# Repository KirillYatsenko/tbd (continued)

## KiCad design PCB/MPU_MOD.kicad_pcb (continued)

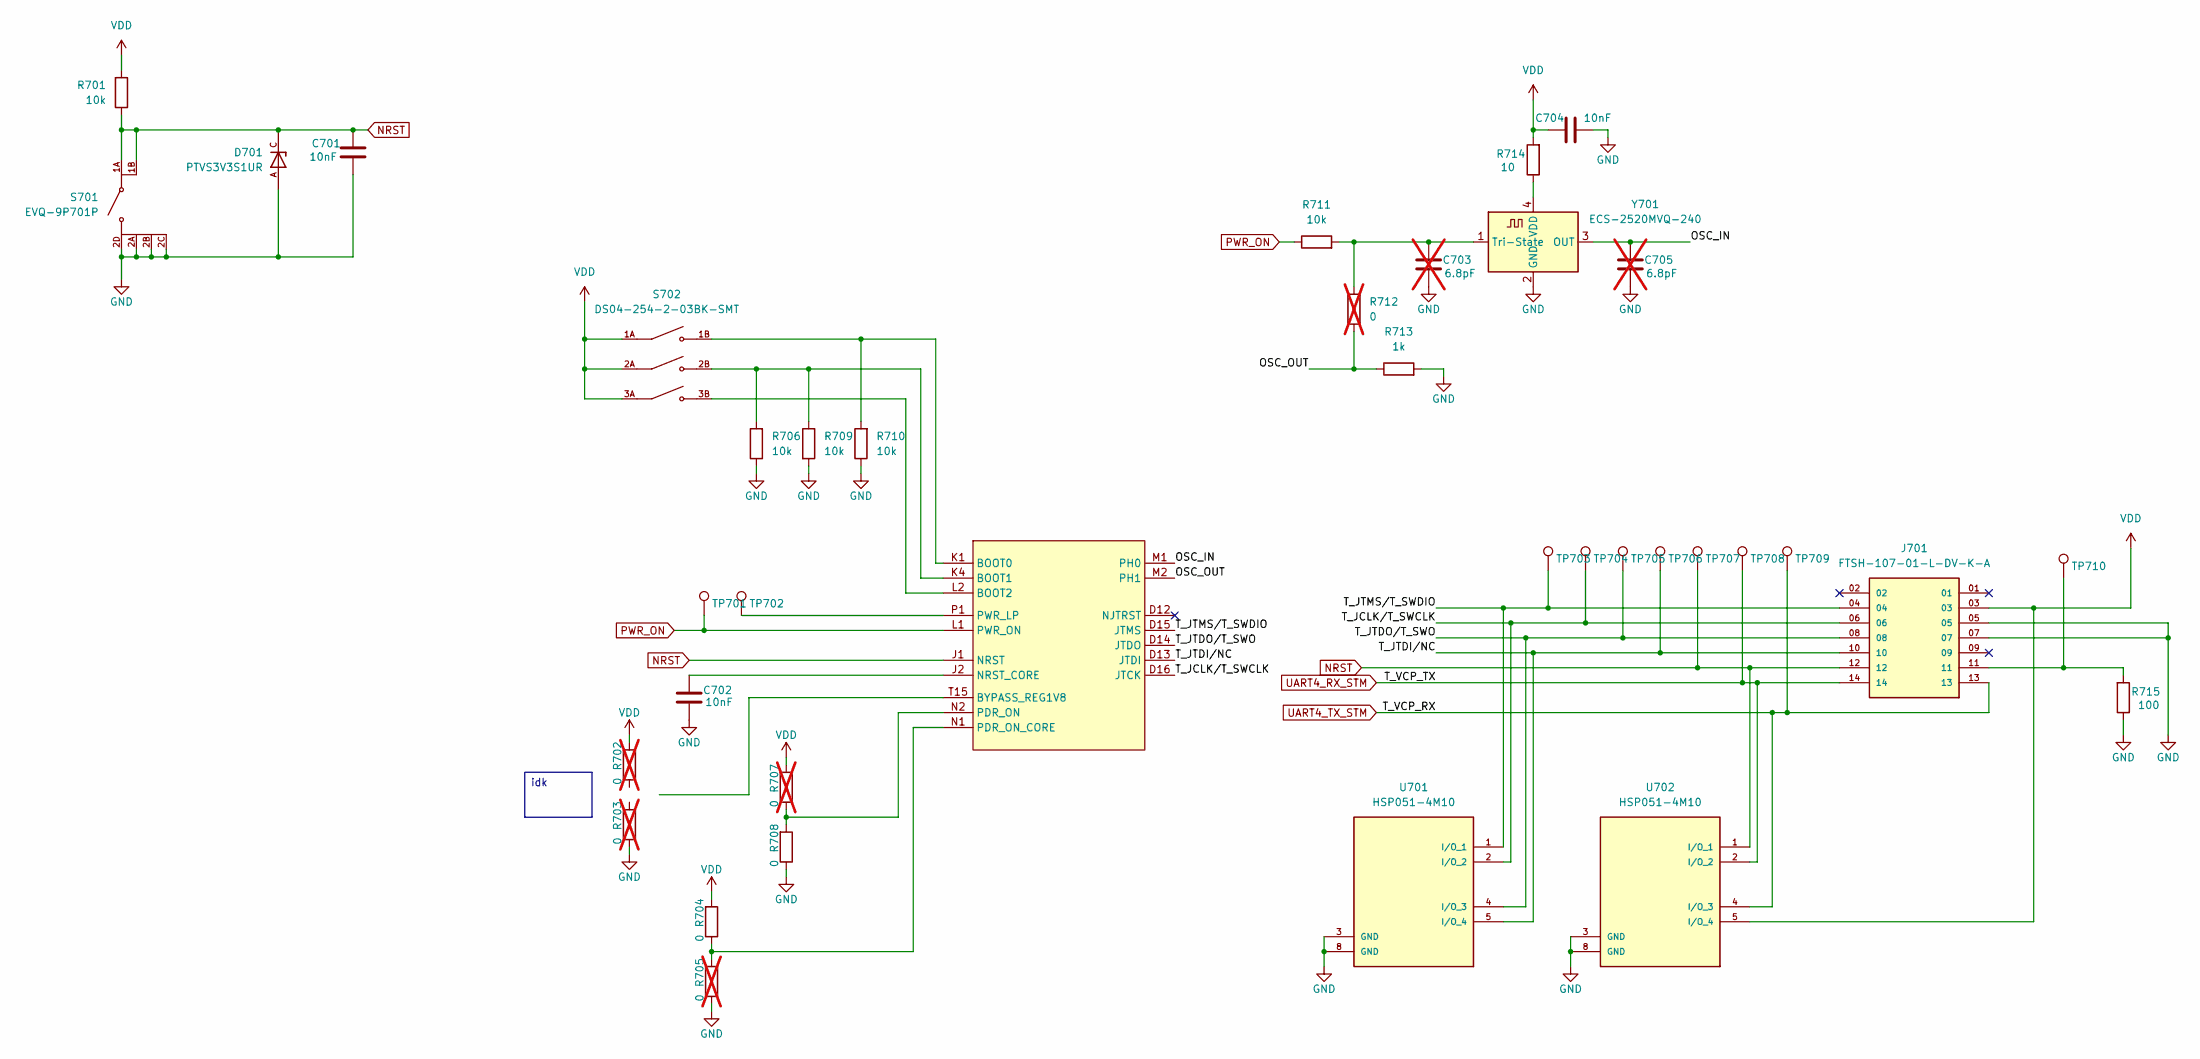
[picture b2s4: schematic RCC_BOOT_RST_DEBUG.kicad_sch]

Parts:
C701, C702, C704: 10nF; C_0402_1005Metric; Mouser P/N 81-GRM155R71C103KA1J
C703, C705: 6.8pF; C_0402_1005Metric; not fitted
D701: PTVS3V3S1UR; TVS_PTVS3V3S1UR; PARTREV Rev. 3
J701: FTSH-107-01-L-DV-K-A; SAMTEC_FTSH-107-01-L-DV-K-A; PARTREV H
R701, R706, R709, R710, R711: 10k; R_0402_1005Metric
R702, R703, R705, R707, R712: 0; R_0402_1005Metric; not fitted
R704, R708: 0; R_0402_1005Metric
R713: 1k; R_0402_1005Metric
R714: 10; R_0402_1005Metric
R715: 100; R_0402_1005Metric
S701: EVQ-9P701P; SW_EVQ-9P701P; PARTREV N/A
S702: DS04-254-2-03BK-SMT; SW_DS04-254-2-03BK-SMT; PARTREV V0.0
TP701, TP702, TP703, TP704, TP705, TP706, TP707, TP708, TP709, TP710: TestPoint; TP_0.5mm
U301: STM32MP157FABx; ST_LFBGA-354_16x16mm_Layout19x19_P0.8mm
U701, U702: HSP051-4M10; IC_HSP051-4M10; Mouser P/N 511-HSP051-4M10
Y701: ECS-2520MVQ-240; Oscillator_SMD_ECS_2520MV-xxx-xx-4Pin_2.5x2.0mm; Mouser P/N 520-E2520MVQ240BSTR

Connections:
/RCC_BOOT_RST_DEBUG/OSC_IN: C705.2, U301.M1 (PH0), Y701.3 (OUT)
/RCC_BOOT_RST_DEBUG/OSC_OUT: R712.1, R713.1, U301.M2 (PH1)
/RCC_BOOT_RST_DEBUG/T_JCLK/T_SWCLK: J701.06, TP704.1, U301.D16 (JTCK), U701.2 (I/O_2), U701.9 (NC)
/RCC_BOOT_RST_DEBUG/T_JTDI/NC: J701.10, TP706.1, U301.D13 (JTDI), U701.5 (I/O_4), U701.6 (NC)
/RCC_BOOT_RST_DEBUG/T_JTDO/T_SWO: J701.08, TP705.1, U301.D14 (JTDO), U701.4 (I/O_3), U701.7 (NC)
/RCC_BOOT_RST_DEBUG/T_JTMS/T_SWDIO: J701.04, TP703.1, U301.D15 (JTMS), U701.1 (I/O_1), U701.10 (NC)
GND: C701.1, C702.1, C703.1, C704.2, C705.1, D701.A, J701.05, J701.07, R703.1, R705.1, R706.1, R708.1, R709.2, R710.1, R713.2, R715.1, S701.2A, S701.2B, S701.2C, S701.2D, U701.3 (GND), U701.8 (GND), U702.3 (GND), U702.8 (GND), Y701.2 (GND); also elsewhere on the board
NRST: C701.2, D701.C, J701.12, R701.1, S701.1A, S701.1B, TP707.1, U301.J1 (NRST), U702.1 (I/O_1), U702.10 (NC); also elsewhere on the board
unnamed: J701.11, R715.2, TP710.1
unnamed: R710.2, S702.1B, U301.K1 (BOOT0)
unnamed: R706.2, R709.1, S702.2B, U301.K4 (BOOT1)
unnamed: S702.3B, U301.L2 (BOOT2)
unnamed: C702.2, U301.J2 (NRST_CORE)
unnamed: R707.1, R708.2, U301.N2 (PDR_ON)
unnamed: R704.1, R705.2, U301.N1 (PDR_ON_CORE)
unnamed: TP702.1, U301.P1 (PWR_LP)
unnamed: C703.2, R711.2, R712.2, Y701.1 (Tri-State)
unnamed: R714.1, Y701.4 (VDD)
PWR_ON: R711.1, TP701.1, U301.L1 (PWR_ON); also elsewhere on the board
UART4_RX_STM: J701.14, TP708.1, U702.2 (I/O_2), U702.9 (NC); also elsewhere on the board
UART4_TX_STM: J701.13, TP709.1, U702.4 (I/O_3), U702.7 (NC); also elsewhere on the board
VDD: C704.1, J701.03, R701.2, R702.2, R704.2, R707.2, R714.2, S702.1A, S702.2A, S702.3A, U702.5 (I/O_4), U702.6 (NC); also elsewhere on the board

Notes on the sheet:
idk

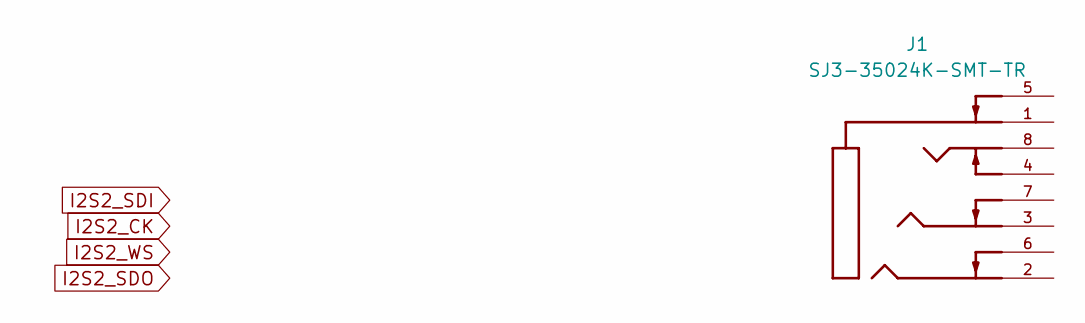
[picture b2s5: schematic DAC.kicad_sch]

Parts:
J1: SJ3-35024K-SMT-TR; SAMESKY_SJ3-35024K-SMT-TR; PARTREV 1.0

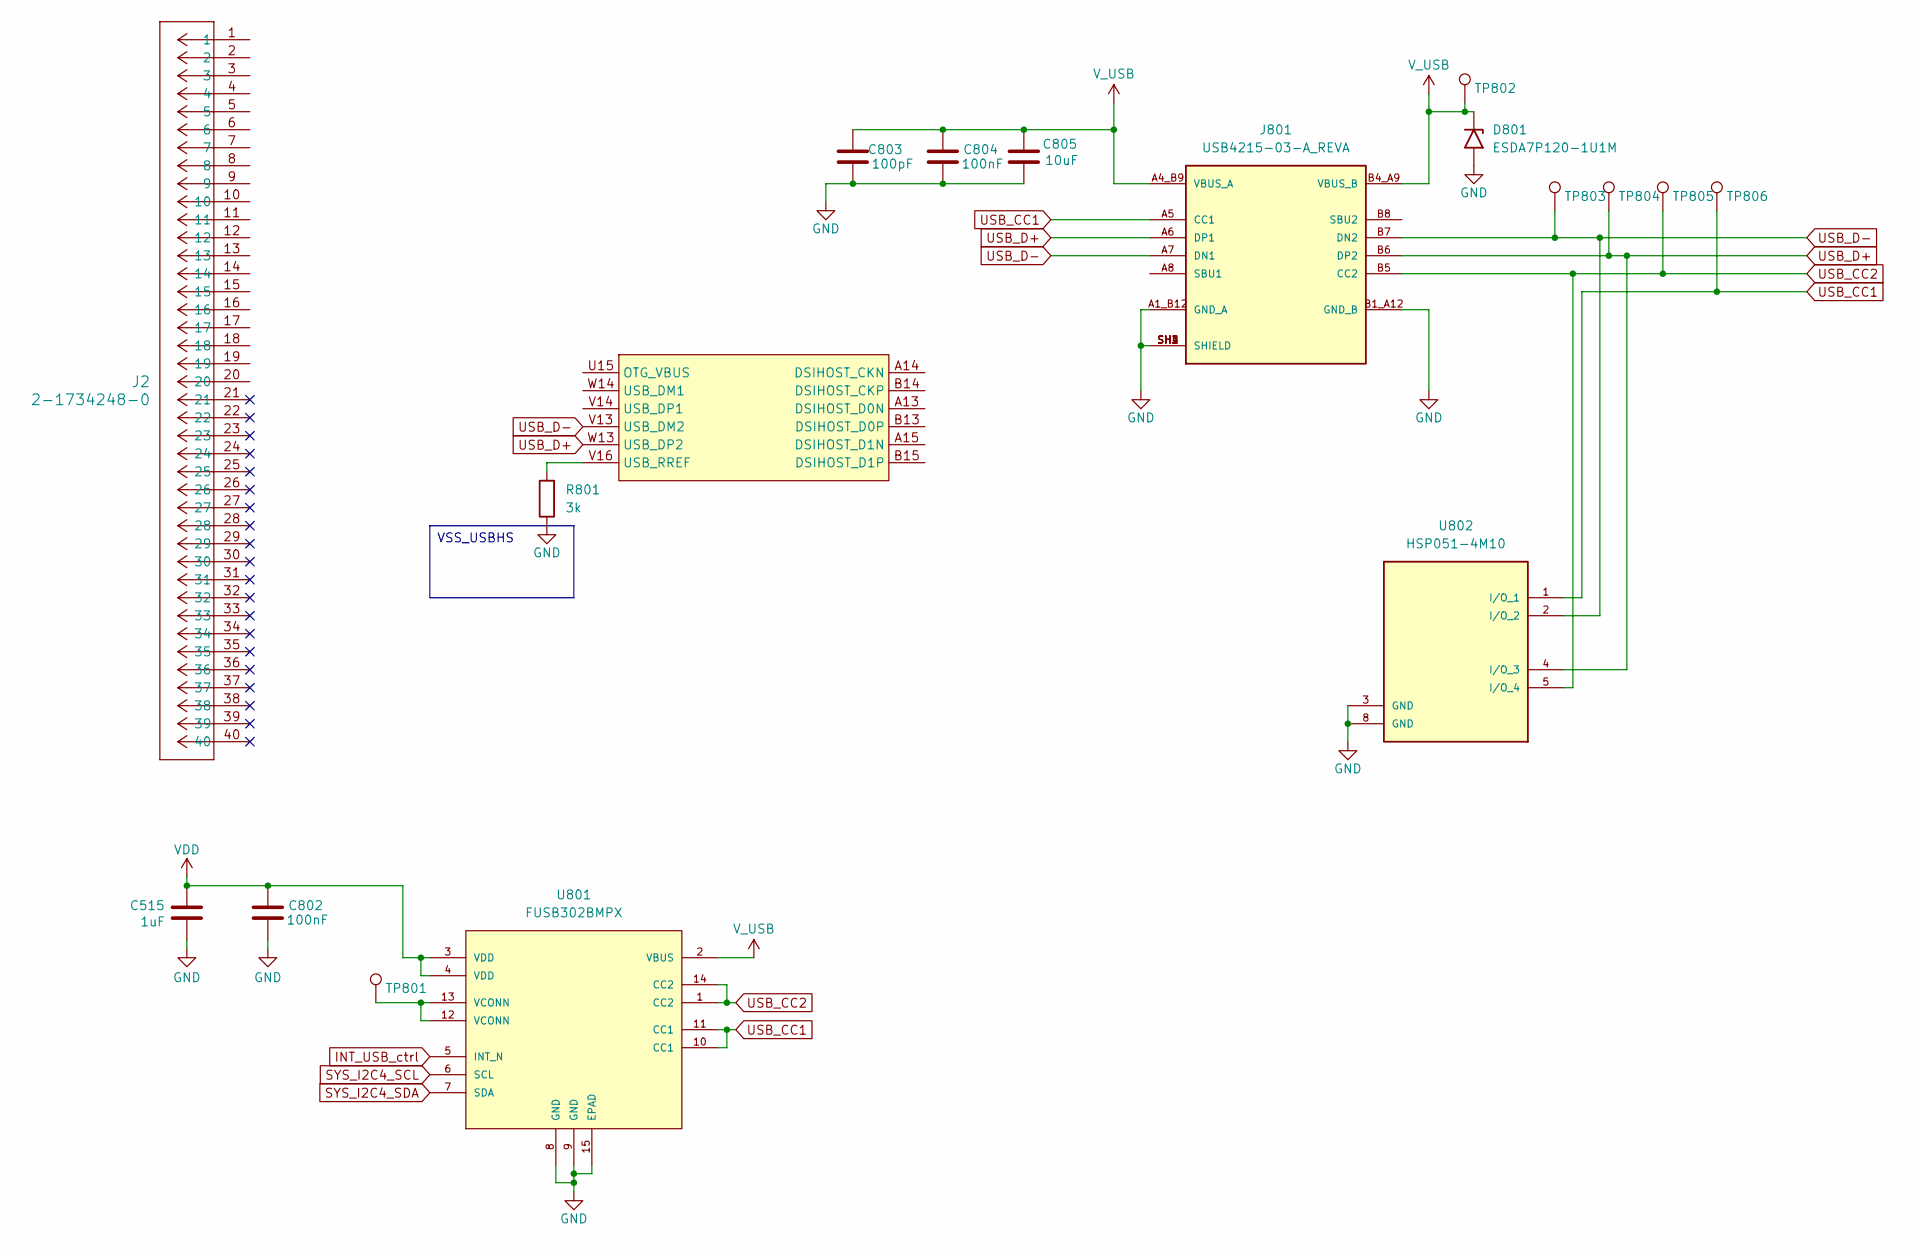
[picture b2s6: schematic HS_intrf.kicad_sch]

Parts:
C515: 1uF; C_0402_1005Metric; Mouser P/N 81-GRM155R61E105KA2D
C802, C804: 100nF; C_0402_1005Metric; Mouser P/N 81-GRM155R61E104KA7J
C803: 100pF; C_0402_1005Metric
C805: 10uF; C_0603_1608Metric; Mouser P/N 81-GRT188R61A106KE3D
D801: ESDA7P120-1U1M; DIODE_ESDA7P120-1U1M_STM
J2: 2-1734248-0; CONN_2-1734248-0_TYCO
J801: USB4215-03-A_REVA; GCT_USB4215-03-A_REVA; PARTREV A
R801: 3k; R_0402_1005Metric
TP801, TP802, TP803, TP804, TP805, TP806: TestPoint; TP_0.5mm
U301: STM32MP157FABx; ST_LFBGA-354_16x16mm_Layout19x19_P0.8mm
U801: FUSB302BMPX; MLP14_2P5X2P5_ONS; MANUFACTURER_PART_NUMBER FUSB302BMPX
U802: HSP051-4M10; IC_HSP051-4M10; Mouser P/N 511-HSP051-4M10

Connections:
GND: C515.2, C802.1, C803.2, C804.1, C805.1, D801.2 (A2), J801.A1_B12 (GND_A), J801.B1_A12 (GND_B), J801.SH1 (SHIELD), J801.SH2 (SHIELD), J801.SH3 (SHIELD), J801.SH4 (SHIELD), R801.1, U801.8 (GND), U801.9 (GND), U801.15 (EPAD), U802.3 (GND), U802.8 (GND); also elsewhere on the board
INT_USB_ctrl: U801.5 (INT_N)
unnamed: TP801.1, U801.12 (VCONN), U801.13 (VCONN)
unnamed: R801.2, U301.V16 (USB_RREF)
SYS_I2C4_SCL: U801.6 (SCL); also elsewhere on the board
SYS_I2C4_SDA: U801.7 (SDA); also elsewhere on the board
USB_CC1: J801.A5 (CC1), TP806.1, U801.10 (CC1), U801.11 (CC1), U802.1 (I/O_1), U802.10 (NC)
USB_CC2: J801.B5 (CC2), TP805.1, U801.1 (CC2), U801.14 (CC2), U802.5 (I/O_4), U802.6 (NC)
USB_D+: J801.A6 (DP1), J801.B6 (DP2), TP804.1, U301.W13 (USB_DP2), U802.4 (I/O_3), U802.7 (NC)
USB_D-: J801.A7 (DN1), J801.B7 (DN2), TP803.1, U301.V13 (USB_DM2), U802.2 (I/O_2), U802.9 (NC)
VDD: C515.1, C802.2, U801.3 (VDD), U801.4 (VDD); also elsewhere on the board
V_USB: C803.1, C804.2, C805.2, D801.1 (A1), J801.A4_B9 (VBUS_A), J801.B4_A9 (VBUS_B), TP802.1, U801.2 (VBUS); also elsewhere on the board

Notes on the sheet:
VSS_USBHS

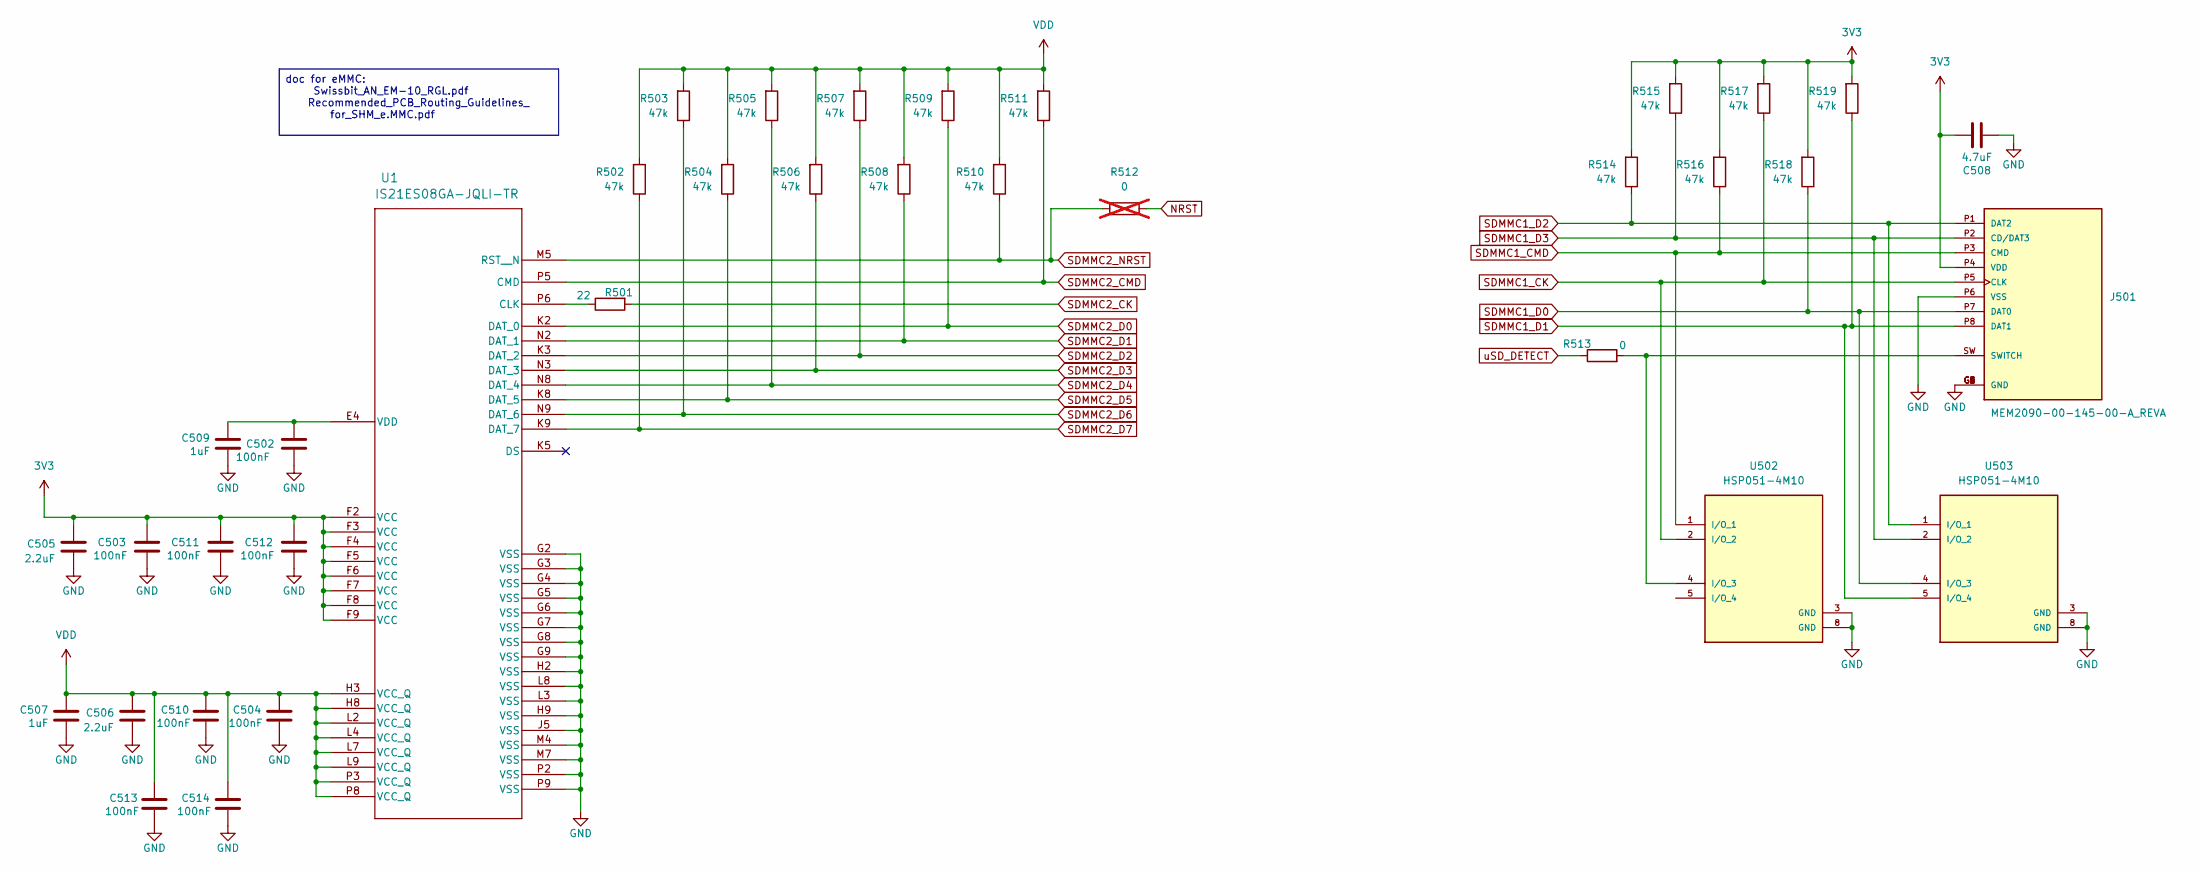
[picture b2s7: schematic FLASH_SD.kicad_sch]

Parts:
C502, C503, C504, C510, C511, C512, C513, C514: 100nF; C_0402_1005Metric; Mouser P/N 81-GRM155R61E104KA7J
C505, C506: 2.2uF; C_0402_1005Metric; Mouser P/N 81-GRT153R60J225ME3D
C507, C509: 1uF; C_0402_1005Metric; Mouser P/N 81-GRM155R61E105KA2D
C508: 4.7uF; C_0402_1005Metric; Mouser P/N 81-GRM155R60J475ME7J
J501: MEM2090-00-145-00-A_REVA; GCT_MEM2090-00-145-00-A_REVA; Mouser P/N 640-MEM20900014500A
R501: 22; R_0402_1005Metric
R502, R503, R504, R505, R506, R507, R508, R509, R510, R511, R514, R515, R516, R517, R518, R519: 47k; R_0402_1005Metric
R512: 0; R_0402_1005Metric; not fitted
R513: 0; R_0402_1005Metric
U1: IS21ES08GA-JQLI-TR; FBGA100_ISI
U502, U503: HSP051-4M10; IC_HSP051-4M10; Mouser P/N 511-HSP051-4M10

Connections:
3V3: C503.2, C505.1, C508.2, C511.2, C512.2, J501.P4 (VDD), R514.2, R515.2, R516.2, R517.2, R518.2, R519.2, U1.F2 (VCC), U1.F3 (VCC), U1.F4 (VCC), U1.F5 (VCC), U1.F6 (VCC), U1.F7 (VCC), U1.F8 (VCC), U1.F9 (VCC); also elsewhere on the board
GND: C502.1, C503.1, C504.1, C505.2, C506.2, C507.2, C508.1, C509.2, C510.1, C511.1, C512.1, C513.1, C514.1, J501.G1 (GND), J501.G2 (GND), J501.G3 (GND), J501.G4 (GND), J501.G5 (GND), J501.G6 (GND), J501.P6 (VSS), U1.G2 (VSS), U1.G3 (VSS), U1.G4 (VSS), U1.G5 (VSS), U1.G6 (VSS), U1.G7 (VSS), U1.G8 (VSS), U1.G9 (VSS), U1.H2 (VSS), U1.H9 (VSS), U1.J5 (VSS), U1.L3 (VSS), U1.L8 (VSS), U1.M4 (VSS), U1.M7 (VSS), U1.P2 (VSS), U1.P9 (VSS), U502.3 (GND), U502.8 (GND), U503.3 (GND), U503.8 (GND); also elsewhere on the board
NRST: R512.1; also elsewhere on the board
unnamed: J501.SW (SWITCH), R513.2, U502.4 (I/O_3), U502.7 (NC)
unnamed: R501.1, U1.P6 (CLK)
unnamed: C502.2, C509.1, U1.E4 (VDD)
unnamed: U502.5 (I/O_4), U502.6 (NC)
SDMMC1_CK: J501.P5 (CLK), R517.1, U502.2 (I/O_2), U502.9 (NC); also elsewhere on the board
SDMMC1_CMD: J501.P3 (CMD), R516.1, U502.1 (I/O_1), U502.10 (NC); also elsewhere on the board
SDMMC1_D0: J501.P7 (DAT0), R518.1, U503.4 (I/O_3), U503.7 (NC); also elsewhere on the board
SDMMC1_D1: J501.P8 (DAT1), R519.1, U503.5 (I/O_4), U503.6 (NC); also elsewhere on the board
SDMMC1_D2: J501.P1 (DAT2), R514.1, U503.1 (I/O_1), U503.10 (NC); also elsewhere on the board
SDMMC1_D3: J501.P2 (CD/DAT3), R515.1, U503.2 (I/O_2), U503.9 (NC); also elsewhere on the board
SDMMC2_CK: R501.2; also elsewhere on the board
SDMMC2_CMD: R511.1, U1.P5 (CMD); also elsewhere on the board
SDMMC2_D0: R509.1, U1.K2 (DAT_0); also elsewhere on the board
SDMMC2_D1: R508.1, U1.N2 (DAT_1); also elsewhere on the board
SDMMC2_D2: R507.1, U1.K3 (DAT_2); also elsewhere on the board
SDMMC2_D3: R506.1, U1.N3 (DAT_3); also elsewhere on the board
SDMMC2_D4: R505.1, U1.N8 (DAT_4); also elsewhere on the board
SDMMC2_D5: R504.1, U1.K8 (DAT_5); also elsewhere on the board
SDMMC2_D6: R503.1, U1.N9 (DAT_6); also elsewhere on the board
SDMMC2_D7: R502.1, U1.K9 (DAT_7); also elsewhere on the board
SDMMC2_NRST: R510.1, R512.2, U1.M5 (RST__N)
VDD: C504.2, C506.1, C507.1, C510.2, C513.2, C514.2, R502.2, R503.2, R504.2, R505.2, R506.2, R507.2, R508.2, R509.2, R510.2, R511.2, U1.H3 (VCC_Q), U1.H8 (VCC_Q), U1.L2 (VCC_Q), U1.L4 (VCC_Q), U1.L7 (VCC_Q), U1.L9 (VCC_Q), U1.P3 (VCC_Q), U1.P8 (VCC_Q); also elsewhere on the board
uSD_DETECT: R513.1; also elsewhere on the board

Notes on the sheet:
doc for eMMC: Swissbit_AN_EM-10_RGL.pdf Recommended_PCB_Routing_Guidelines_ for_SHM_e.MMC.pdf

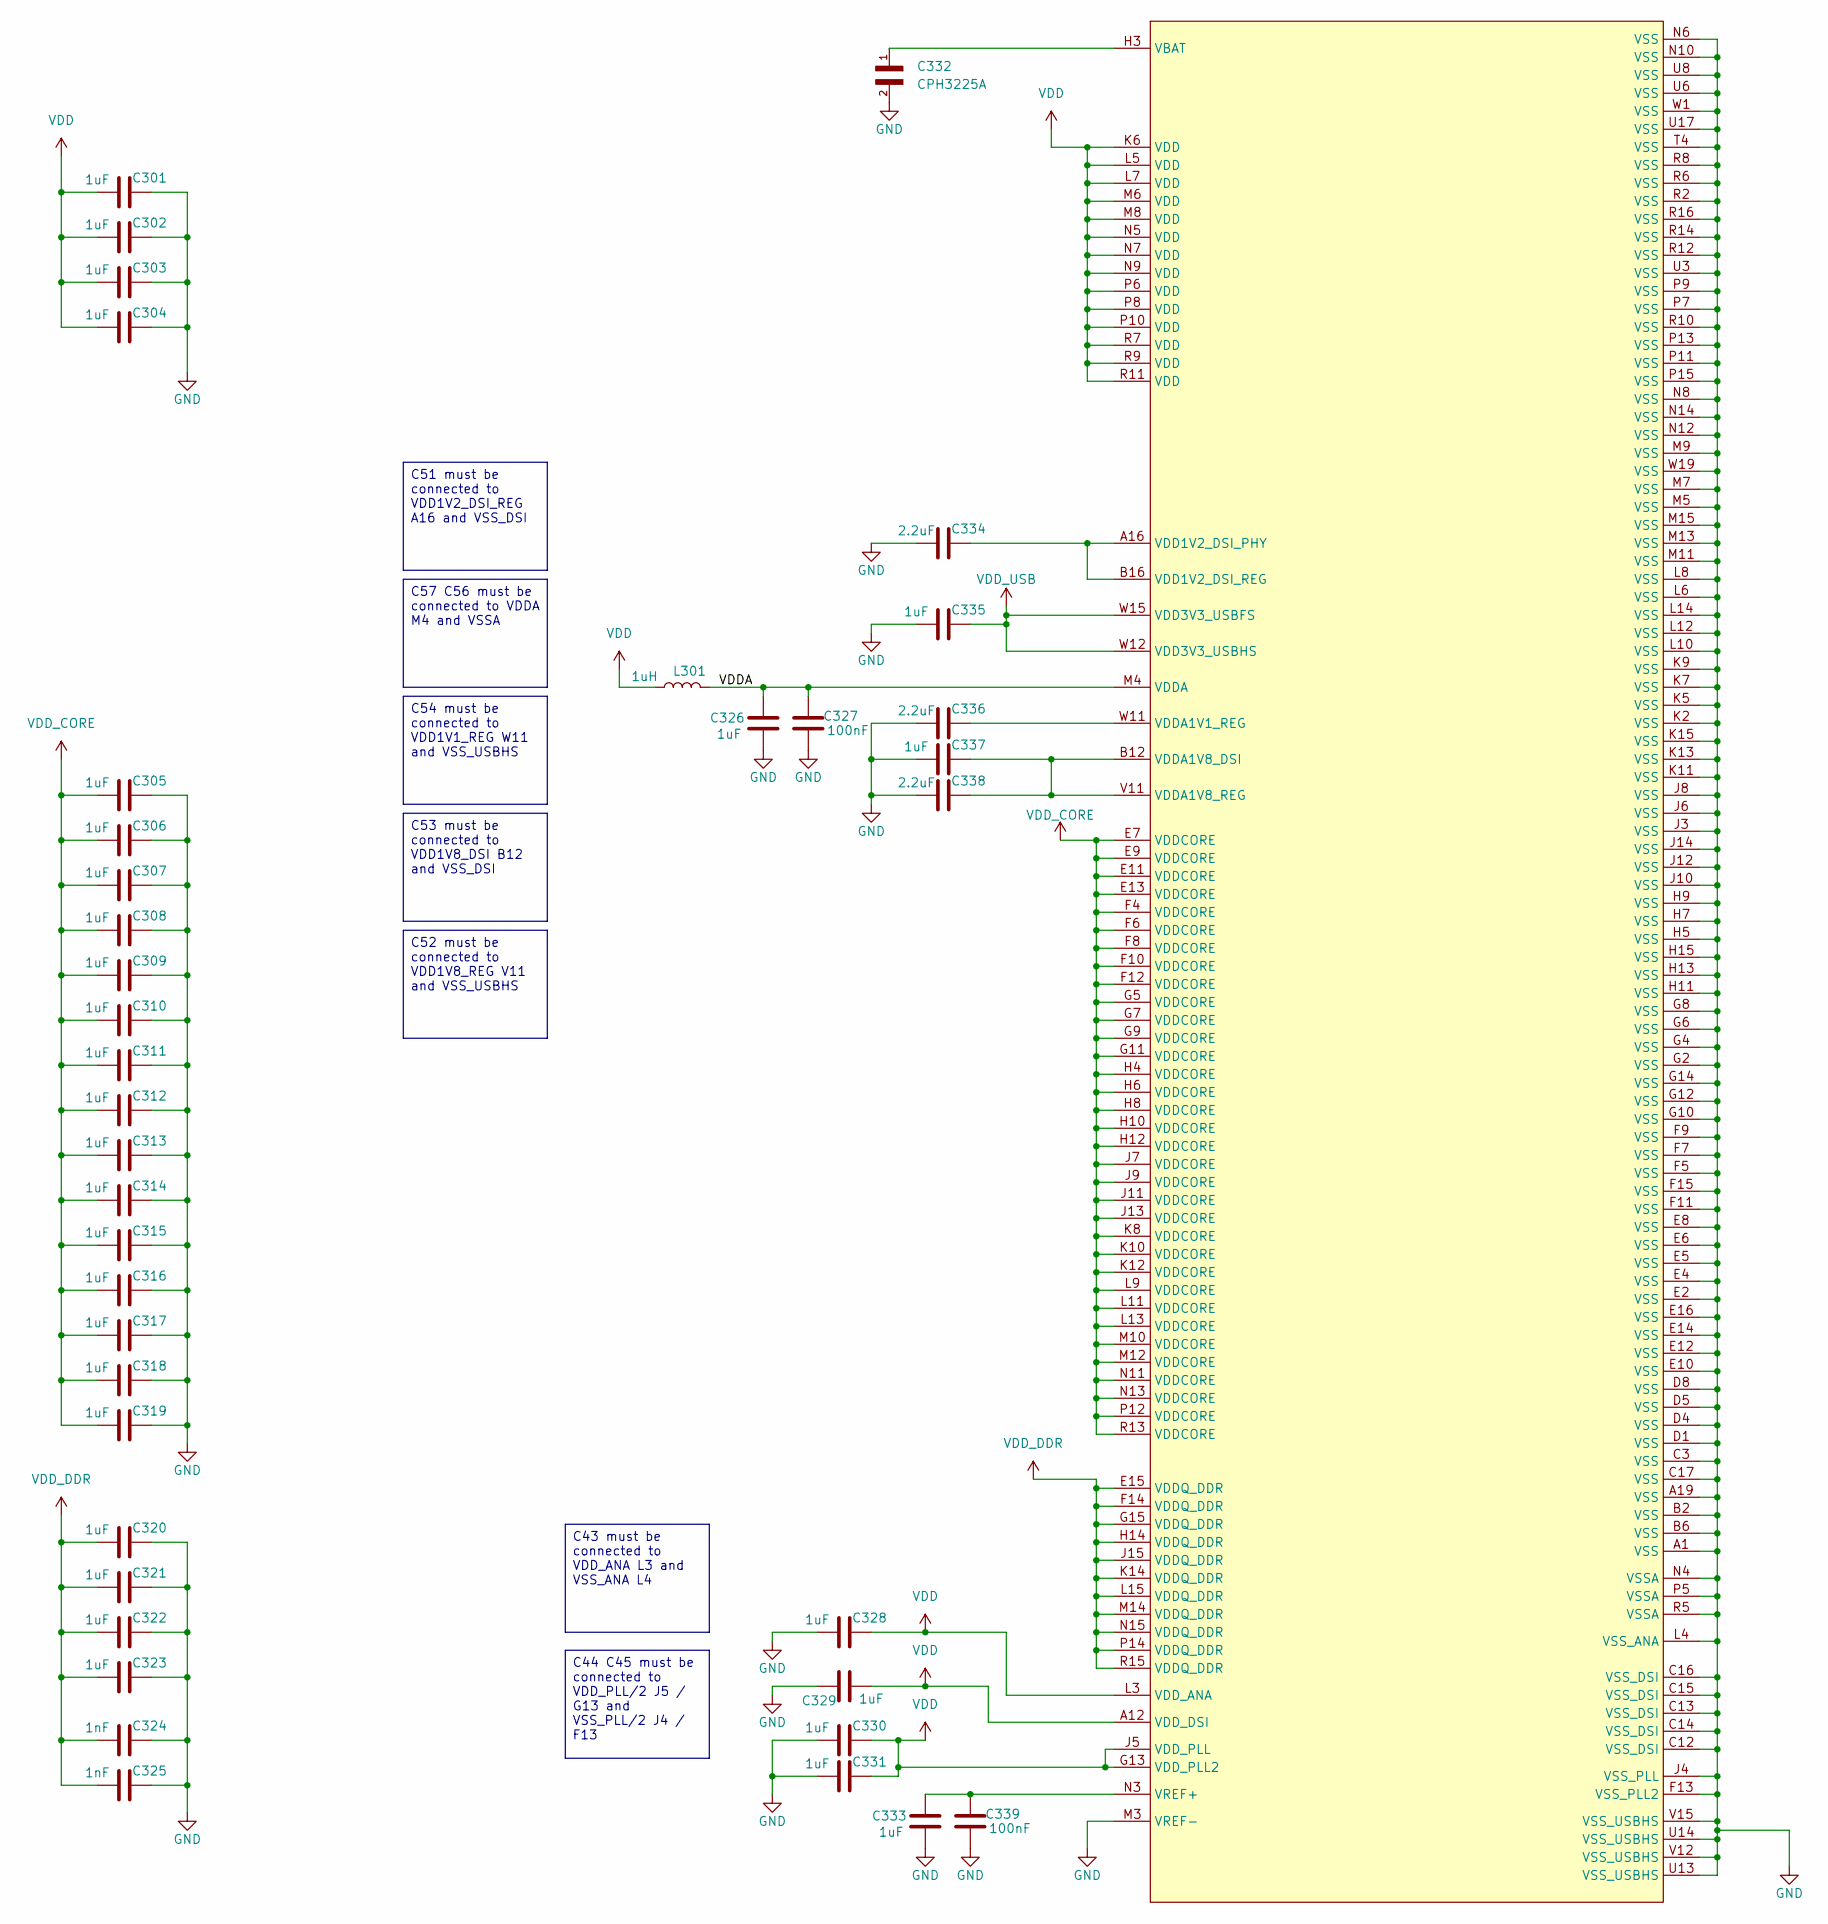
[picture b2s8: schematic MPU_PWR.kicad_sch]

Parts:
C301, C302, C303, C304, C305, C306, C307, C308, C309, C310, C311, C312, C313, C314, C315, C316, C317, C318, C319, C320, C321, C322, C323, C326, C328, C329, C330, C331, C333, C335, C337: 1uF; C_0402_1005Metric; Mouser P/N 81-GRM155R61E105KA2D
C324, C325: 1nF; C_0402_1005Metric; Mouser P/N 81-GRM155R70J102KA1D
C327, C339: 100nF; C_0402_1005Metric; Mouser P/N 81-GRM155R61E104KA7J
C332: CPH3225A; CAPCP3225X100N
C334, C336, C338: 2.2uF; C_0402_1005Metric; Mouser P/N 81-GRT153R60J225ME3D
L301: 1uH; L_0603_1608Metric; Mouser P/N 810-MLZ1608M4R7WT000
U301: STM32MP157FABx; ST_LFBGA-354_16x16mm_Layout19x19_P0.8mm

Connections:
GND: C301.1, C302.1, C303.1, C304.1, C305.1, C306.1, C307.1, C308.1, C309.1, C310.1, C311.1, C312.1, C313.1, C314.1, C315.1, C316.1, C317.1, C318.1, C319.1, C320.1, C321.1, C322.1, C323.1, C324.1, C325.1, C326.2, C327.2, C328.2, C329.1, C330.2, C331.2, C332.2, C333.2, C334.2, C335.2, C336.2, C337.2, C338.2, C339.2, U301.A1 (VSS), U301.A19 (VSS), U301.B2 (VSS), U301.B6 (VSS), U301.C3 (VSS), U301.C12 (VSS_DSI), U301.C13 (VSS_DSI), U301.C14 (VSS_DSI), U301.C15 (VSS_DSI), U301.C16 (VSS_DSI), U301.C17 (VSS), U301.D1 (VSS), U301.D4 (VSS), U301.D5 (VSS), U301.D8 (VSS), U301.E2 (VSS), U301.E4 (VSS), U301.E5 (VSS), U301.E6 (VSS), U301.E8 (VSS), U301.E10 (VSS), U301.E12 (VSS), U301.E14 (VSS), U301.E16 (VSS), U301.F5 (VSS), U301.F7 (VSS), U301.F9 (VSS), U301.F11 (VSS), U301.F13 (VSS_PLL2), U301.F15 (VSS), U301.G2 (VSS), U301.G4 (VSS), U301.G6 (VSS), U301.G8 (VSS), U301.G10 (VSS), U301.G12 (VSS), U301.G14 (VSS), U301.H5 (VSS), U301.H7 (VSS), U301.H9 (VSS), U301.H11 (VSS), U301.H13 (VSS), U301.H15 (VSS), U301.J3 (VSS), U301.J4 (VSS_PLL), U301.J6 (VSS), U301.J8 (VSS), U301.J10 (VSS), U301.J12 (VSS), U301.J14 (VSS), U301.K2 (VSS), U301.K5 (VSS), U301.K7 (VSS), U301.K9 (VSS), U301.K11 (VSS), U301.K13 (VSS), U301.K15 (VSS), U301.L4 (VSS_ANA), U301.L6 (VSS), U301.L8 (VSS), U301.L10 (VSS), U301.L12 (VSS), U301.L14 (VSS), U301.M3 (VREF-), U301.M5 (VSS), U301.M7 (VSS), U301.M9 (VSS), U301.M11 (VSS), U301.M13 (VSS), U301.M15 (VSS), U301.N4 (VSSA), U301.N6 (VSS), U301.N8 (VSS), U301.N10 (VSS), U301.N12 (VSS), U301.N14 (VSS), U301.P5 (VSSA), U301.P7 (VSS), U301.P9 (VSS), U301.P11 (VSS), U301.P13 (VSS), U301.P15 (VSS), U301.R2 (VSS), U301.R5 (VSSA), U301.R6 (VSS), U301.R8 (VSS), U301.R10 (VSS), U301.R12 (VSS), U301.R14 (VSS), U301.R16 (VSS), U301.T4 (VSS), U301.U3 (VSS), U301.U6 (VSS), U301.U8 (VSS), U301.U13 (VSS_USBHS), U301.U14 (VSS_USBHS), U301.U17 (VSS), U301.V12 (VSS_USBHS), U301.V15 (VSS_USBHS), U301.W1 (VSS), U301.W19 (VSS); also elsewhere on the board
unnamed: C332.1, U301.H3 (VBAT)
unnamed: C334.1, U301.A16 (VDD1V2_DSI_PHY), U301.B16 (VDD1V2_DSI_REG)
unnamed: C336.1, U301.W11 (VDDA1V1_REG)
unnamed: C337.1, C338.1, U301.B12 (VDDA1V8_DSI), U301.V11 (VDDA1V8_REG)
unnamed: C326.1, C327.1, L301.2, U301.M4 (VDDA)
unnamed: C333.1, C339.1, U301.N3 (VREF+)
VDD: C301.2, C302.2, C303.2, C304.2, C328.1, C329.2, C330.1, C331.1, L301.1, U301.A12 (VDD_DSI), U301.G13 (VDD_PLL2), U301.J5 (VDD_PLL), U301.K6 (VDD), U301.L3 (VDD_ANA), U301.L5 (VDD), U301.L7 (VDD), U301.M6 (VDD), U301.M8 (VDD), U301.N5 (VDD), U301.N7 (VDD), U301.N9 (VDD), U301.P6 (VDD), U301.P8 (VDD), U301.P10 (VDD), U301.R7 (VDD), U301.R9 (VDD), U301.R11 (VDD); also elsewhere on the board
VDD_CORE: C305.2, C306.2, C307.2, C308.2, C309.2, C310.2, C311.2, C312.2, C313.2, C314.2, C315.2, C316.2, C317.2, C318.2, C319.2, U301.E7 (VDDCORE), U301.E9 (VDDCORE), U301.E11 (VDDCORE), U301.E13 (VDDCORE), U301.F4 (VDDCORE), U301.F6 (VDDCORE), U301.F8 (VDDCORE), U301.F10 (VDDCORE), U301.F12 (VDDCORE), U301.G5 (VDDCORE), U301.G7 (VDDCORE), U301.G9 (VDDCORE), U301.G11 (VDDCORE), U301.H4 (VDDCORE), U301.H6 (VDDCORE), U301.H8 (VDDCORE), U301.H10 (VDDCORE), U301.H12 (VDDCORE), U301.J7 (VDDCORE), U301.J9 (VDDCORE), U301.J11 (VDDCORE), U301.J13 (VDDCORE), U301.K8 (VDDCORE), U301.K10 (VDDCORE), U301.K12 (VDDCORE), U301.L9 (VDDCORE), U301.L11 (VDDCORE), U301.L13 (VDDCORE), U301.M10 (VDDCORE), U301.M12 (VDDCORE), U301.N11 (VDDCORE), U301.N13 (VDDCORE), U301.P12 (VDDCORE), U301.R13 (VDDCORE); also elsewhere on the board
VDD_DDR: C320.2, C321.2, C322.2, C323.2, C324.2, C325.2, U301.E15 (VDDQ_DDR), U301.F14 (VDDQ_DDR), U301.G15 (VDDQ_DDR), U301.H14 (VDDQ_DDR), U301.J15 (VDDQ_DDR), U301.K14 (VDDQ_DDR), U301.L15 (VDDQ_DDR), U301.M14 (VDDQ_DDR), U301.N15 (VDDQ_DDR), U301.P14 (VDDQ_DDR), U301.R15 (VDDQ_DDR); also elsewhere on the board
VDD_USB: C335.1, U301.W12 (VDD3V3_USBHS), U301.W15 (VDD3V3_USBFS); also elsewhere on the board

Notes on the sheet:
C43 must be connected to VDD_ANA L3 and VSS_ANA L4
C54 must be connected to VDD1V1_REG W11 and VSS_USBHS
C51 must be connected to VDD1V2_DSI_REG A16 and VSS_DSI
C57 C56 must be connected to VDDA M4 and VSSA
C52 must be connected to VDD1V8_REG V11 and VSS_USBHS
C53 must be connected to VDD1V8_DSI B12 and VSS_DSI
C44 C45 must be connected to VDD_PLL/2 J5 / G13 and VSS_PLL/2 J4 / F13

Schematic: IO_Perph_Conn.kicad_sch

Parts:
C601, C602: 6.8pF; C_0402_1005Metric
D601: LED_B; LED_0402_1005Metric
D602: LED_R; LED_0402_1005Metric
R601, R602: R_0402_1005Metric
R603, R604: 4k7; R_0402_1005Metric
S601, S602, S603, S604, S605: EVQ-9P701P; SW_EVQ-9P701P; PARTREV N/A
TP601, TP602: TestPoint; TP_0.5mm
U301: STM32MP157FABx; ST_LFBGA-354_16x16mm_Layout19x19_P0.8mm
Y601: NX2012SA-32.768K; XTAL_NX2012SA-32.768K-STD-MUB-1

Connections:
3V3: R601.2, R602.2; also elsewhere on the board
GND: C601.1, C602.2; also elsewhere on the board
I2S1_CK: U301.P4 (PA5), U301.W5 (PB10); also elsewhere on the board
I2S1_SDI: U301.T2 (PC2), U301.T5 (PA6); also elsewhere on the board
I2S1_SDO: U301.T6 (PA7), U301.V2 (PC1); also elsewhere on the board
I2S1_WS: U301.R4 (PA4), U301.V5 (PB12); also elsewhere on the board
unnamed: D601.2 (A), R601.1
unnamed: D601.1 (K), TP601.1, U301.R1 (PA14)
unnamed: D602.2 (A), R602.1
unnamed: D602.1 (K), TP602.1, U301.P2 (PA13)
unnamed: C601.2, U301.H1 (PC14), Y601.2
unnamed: C602.1, U301.H2 (PC15), Y601.1
PMIC_PA0_WKUP_INTR: U301.R3 (PA0); also elsewhere on the board
PWR_SW_WAKE_UP: U301.U4 (PA1); also elsewhere on the board
SDMMC1_CK: U301.C10 (PC12); also elsewhere on the board
SDMMC1_CMD: U301.B10 (PD2); also elsewhere on the board
SDMMC1_D0: U301.C11 (PC8); also elsewhere on the board
SDMMC1_D1: U301.A10 (PC9); also elsewhere on the board
SDMMC1_D2: U301.D11 (PC10); also elsewhere on the board
SDMMC1_D3: U301.A11 (PC11); also elsewhere on the board
SDMMC2_CK: U301.A5 (PE3); also elsewhere on the board
SDMMC2_CMD: U301.A6 (PG6); also elsewhere on the board
SDMMC2_D0: U301.C9 (PB14); also elsewhere on the board
SDMMC2_D1: U301.A8 (PB15); also elsewhere on the board
SDMMC2_D2: U301.A7 (PB3); also elsewhere on the board
SDMMC2_D3: U301.B9 (PB4); also elsewhere on the board
SDMMC2_D4: U301.B8 (PA8); also elsewhere on the board
SDMMC2_D5: U301.C8 (PA9); also elsewhere on the board
SDMMC2_D6: U301.B7 (PE5); also elsewhere on the board
SDMMC2_D7: U301.C6 (PD3); also elsewhere on the board
SDMMC3_CK: U301.A2 (PG15); also elsewhere on the board
SDMMC3_CMD: U301.A3 (PD0); also elsewhere on the board
SDMMC3_D0: U301.A4 (PD1); also elsewhere on the board
SDMMC3_D1: U301.D6 (PD4); also elsewhere on the board
SDMMC3_D2: U301.D7 (PD5); also elsewhere on the board
SDMMC3_D3: U301.B4 (PD7); also elsewhere on the board
SYS_I2C4_SCL: R603.1, U301.T12 (PB6); also elsewhere on the board
SYS_I2C4_SDA: R604.1, U301.U12 (PD13); also elsewhere on the board
UART4_RX_STM: U301.T13 (PB2); also elsewhere on the board
UART4_TX_STM: U301.V6 (PG11); also elsewhere on the board
UART8_CTS_STM: U301.E1 (PE15); also elsewhere on the board
UART8_RTS_STM: U301.D3 (PE14); also elsewhere on the board
UART8_RX_STM: U301.C4 (PE0); also elsewhere on the board
UART8_TX_STM: U301.B1 (PE1); also elsewhere on the board
VDD: R603.2, R604.2; also elsewhere on the board
uSD_DETECT: U301.B5 (PB7); also elsewhere on the board

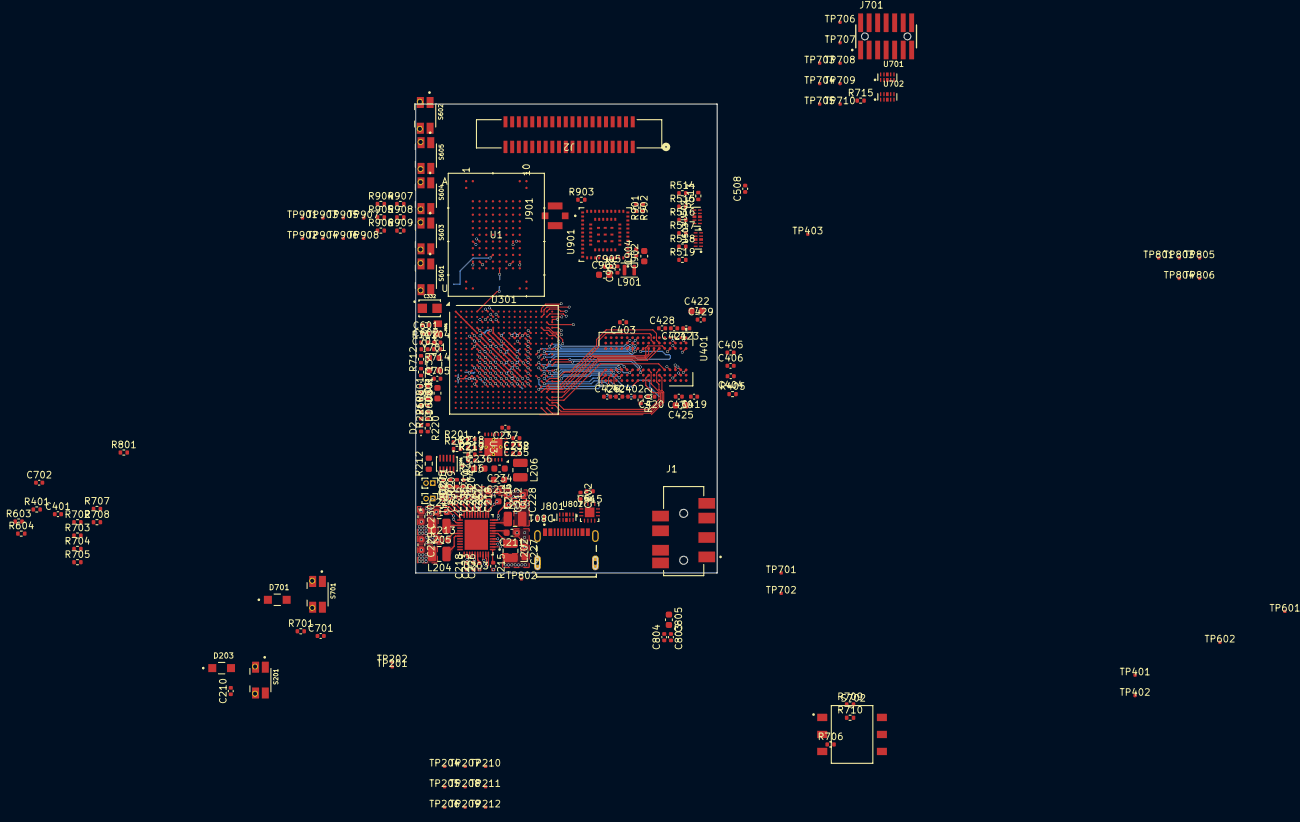
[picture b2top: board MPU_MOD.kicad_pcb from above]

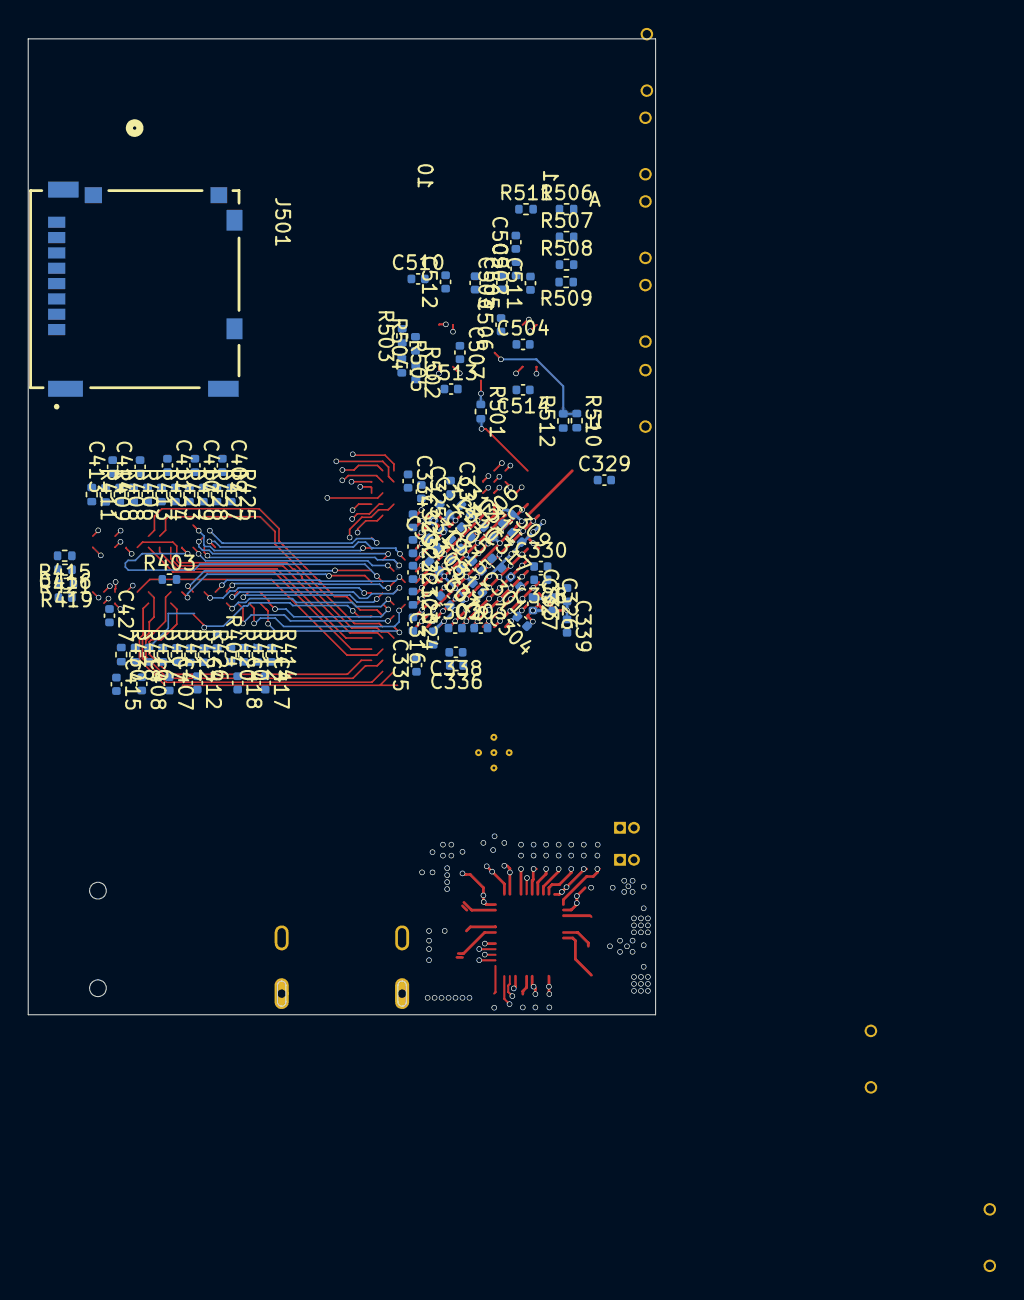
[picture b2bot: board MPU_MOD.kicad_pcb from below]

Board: 8 copper layers, 45.0 x 70.0 mm, 305 parts (103 on the bottom side), 176 nets.

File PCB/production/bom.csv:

Designator,Footprint,Quantity,Value,LCSC Part #
BT201,PinHeader_1x02_P1.00mm_Vertical,1,Battery_Cell,
C204,0402,1,220nF,
"C205, C216, C217, C219, C237, C419, C507, C509, C515",0402,9,1uF,
"C211, C212, C213, C214, C215, C222, C233, C234, C236, C422, C425, C805",0603,12,10uF,
"C218, C220, C221, C223, C224, C225, C226, C235, C508",0402,9,4.7uF,
"C227, C228, C229, C230",0603,4,22uF,
C232,0402,1,47nF,
C238,0402,1,8.2uF,
"C402, C403, C420, C421, C423, C424, C426, C427, C428, C429, C430, C502, C503, C504, C510, C511, C512, C513, C514, C802, C804",0402,21,100nF,
"C505, C506",0402,2,2.2uF,
C803,0402,1,100pF,
D801,DIODE_ESDA7P120-1U1M_STM,1,ESDA7P120-1U1M,
J501,GCT_MEM2090-00-145-00-A_REVA,1,MEM2090-00-145-00-A_REVA,
J801,GCT_USB4215-03-A_REVA,1,USB4215-03-A_REVA,
"L202, L203, L204, L205, L206",1008,5,1uH,
Q1,TRANS_STL9P3LLH6,1,STL9P3LLH6,
"R201, R202, R219, R404",0402,4,10k,
"R209, R210",0402,2,1k,
R212,0603,1,10m,
"R215, R512, R513",0402,3,0,
R216,0402,1,5k25,
R217,0402,1,31k23,
R218,0402,1,317,
R402,0402,1,240,
R403,0402,1,100,
"R406, R407, R408, R409, R410, R411, R412, R413, R414, R415, R416, R417, R418, R419, R420, R421, R422, R423, R424, R425, R426, R427, R428, R429, R430",0402,25,56,
R501,0402,1,22,
"R502, R503, R504, R505, R506, R507, R508, R509, R510, R511",0402,10,47k,
TH201,PinHeader_1x02_P1.00mm_Vertical,1,Thermistor,
"TP203, TP802",TP_0.5mm,2,TestPoint,
U1,FBGA100_ISI,1,IS21ES08GA-JQLI-TR,
U201,SON50P300X200X60-10N,1,STC3115IQT,
U203,QFN40P600X500X80-45N,1,STPMIC1APQR,
U3,BQ24298,1,BQ24298RTWR,
U301,ST_LFBGA-354_16x16mm_Layout19x19_P0.8mm,1,STM32MP157FABx,
U401,BGA96C80P9X16_1400X800X120,1,MT41K256M16TW-107_P,
"U502, U503, U802",IC_HSP051-4M10,3,HSP051-4M10,
U801,MLP14_2P5X2P5_ONS,1,FUSB302BMPX,
U901,XCVR_LBEE5PK2AE-771,1,LBEE5PK2AE-771,
